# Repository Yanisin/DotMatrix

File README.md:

# DotMatrix

## What is this?

A STM32F070CB driving a LED DotMatrix.

## Prerequisities for building Firmware

  * You need an appropriate Cortex-M ARM toolchain. We suggest to use the
  ARM's [GNU Embedded Toolchain for Arm ](https://developer.arm.com/tools-and-software/open-source-software/developer-tools/gnu-toolchain/gnu-rm/downloads).
  Please note that the `gcc-arm-none-eabi` provided by Ubuntu 18.04 is currently broken and can't be used.

  * This project makes use of [libopencm3]()https://github.com/libopencm3/libopencm3) and [ChibiOS](http://www.chibios.org).
  In order to build `libopencm3` you need `Python 2`.

  * To download the firmware, you have two options:
     - Via USB: You need `dfu-util 0.9+` and a USB cable. Please not that `dfu-util 0.8` will not work.
     - Via SWD: You need `openocd` and a `ST-LINK v2 device`
  
  * Optional: `Docker`

You might be interested in some [libopencm3 examples here](https://github.com/libopencm3/libopencm3-examples).

The pull requests there might be an interesting source of information as well.

You will also want to have the manuals for your hardware at hand. These are the most important for software development:
 - Peripherals, memory layout, registers ... : [STM32F030x4/x6/x8/xC and STM32F070x6/xB MCUs](https://www.st.com/resource/en/reference_manual/dm00091010.pdf)
 - Pinouts, Electric Characteristcs, HW variants, clocks ...:
   [STM32F070CB Product Specification](https://www.st.com/resource/en/datasheet/stm32f070cb.pdf)
 - Exceptions (NVIC), instructions ... :
   [ARM® v7-M Architecture Reference Manual](https://static.docs.arm.com/ddi0403/eb/DDI0403E_B_armv7m_arm.pdf)

## Install & Build

Get the code:

    $ git clone https://github.com/libopencm3/libopencm3.git
    $ git clone https://github.com/ChibiOS/ChibiOS.git
    $ git clone https://github.com/Yanisin/DotMatrix.git

We provide a Dockerfile, containing the suggested toolchain, openocd, dfu-util and other tools as well.
You can build the container with:

    $ cd DotMatrix/
    DotMatrix$ docker build -t gcc-arm-none-eabi-8-2018-q4 .

Create a file named `settings.mk` in `DotMatrix/src` and provide an appropriate configuration.
You can use `DotMatrix/src/settings.mk.example` as input. This `settings.mk` works with the Docker container:

```
OPENCM3_DIR ?= /home/dev/app/src/libopencm3
CHIBIOS ?= /home/dev/app/src/ChibiOS
HW_VERSION = "HW_60x60_rev_0_5"
SUDO=
SIM=0
OOCD ?= openocd
OOCD_INTERFACE ?= stlink-v2-1
OOCD_TARGET ?= stm32f0x
```

You can start the container with:

    DotMatrix$ docker run -it --privileged --expose 4444 \
                  -v /dev/bus/usb:/dev/bus/usb \
                  -v `pwd`/../libopencm3:/home/dev/app/src/libopencm3 \
                  -v `pwd`/../ChibiOS:/home/dev/app/src/ChibiOS \
                  -v `pwd`:/home/dev/app \
                  gcc-arm-none-eabi-8-2018-q4:latest /bin/bash

You need to compile `libopencm3` before usage. This has to be done once.
With help of the toolchain container this is:

    dev@59e291eed30d:~/app$ cd src/libopencm3/
    dev@59e291eed30d:~/app/src/libopencm3$ make

ChibiOS is compiled on demand.

To compile the firmware / demo of your interest, just go to the directory and issue `$ make`. For instance:

    dev@59e291eed30d:~/app$ cd src/full/
    dev@59e291eed30d:~/app/src/full$ make

This should result in a binary `build/full.elf`.

### Content of the package

The software demos live in the src directory. There are are three main demos
avaiable:

- `src/stm32f070_miniblink` - a simple demo just blinking the LED
- `src/GameOfLife` - GameOfLife with all connected cells working together.
  Simple communication protocol over UART. The demo uses just libopencm3
  for HW interfacing.
- `src/full` - the 'catch all' demo. Includes GameOfLife and other applications
  that are selectable with an 'applet selector'. Provides a communication
  layer over I2C and UART. Automatically detects the topology of the boards
  at startup and chooses a 'master board'. Is based on an RTOS (ChibiOS).

There are also other small testing projects and a simulator that allows you to
run the 'full' demo on your host machine.

## Flashing

Flashing is done using the `make prg` and `make prg_usb` commands.
See `src/common.mk` for other makefile commands.

### SWD Interface

Attach the SWD interface of the MCU via stlink-v2 programmer and issue `$ make prg`

### USB DFU Bootloaders

There are two USB bootloaders.  One is burnt int the MCU from the manufacturer.
This one can be used in case of emergency to write "more specialized" bootloader stored 
in the FLASH, and that is used the flash the actual firmware.

The MCU itself has a bootloader burnt from the manufacture. This one requires
the Y1 oscillator popullated in order to work. It can be

#### Project Distributed Bootloader

There is a bootloader in `src/dfu`. Among other nice features this bootloader
allows to flash multiple interconnected boards at the same time.
Once compiled it can be flashed to ieach of the MCUs either using the stlink-v2
programer ( using `make prg` commad) or via the MCUs built in bootloader (using
the "make prg_bl" command).

If you want to use this bootloader (recommneded way), issue `$ make prg_usb` in
your project and connect the board over USB (or restart it, if it is already
connected. The flashing process will start as soon as the board reaches the
bootlader (you will see threee dots). If multiple boards are connected and
started at once, the firmware will be loaded to all of them.

The USB part of this bootloader seems to work even without Y1 resonator
populated, but the manufacturer does not say that it should be relyable.
If you have the the Y1 not populated keep this in mind.

#### MCU Manufacturers Bootloader

The MCU has a built in bootloader that is started if the BOOT0 pin is held hight
after reset is released. On the board there is reset circuitry with button.
If you hold this `reset` button for several seconds, you will get the board into
manufacturer provided bootloader. Among other ways (like USART, SPI, I2C) this
bootloader can program the flash via the USB DFU protocol. Use `make prg_bl` to
talk to this bootloader.  This can be used to flash the project bootloader or
have the wonderfull feeling of running bare-metal. If you want to run your
project without the project bootloader, You have to compile the demo with
`NO_BOOTLOADER=1`. 

Keep in mind that you can use this bootloader in USB DFU mode only if there is
the Y1 resonator present. If the Y1 is not present, you will need to use the
stlink-v2 or some other interface that this bootloader can handle even without
oscillator.  For details about this bootloader search for STs AN2606.

## Memory layout

Even though that you are programming C, it is important to know the memory
layout for debugging etc. The makefiles will take care of linking the code
at correct addreses.

ROM is mapped at 0x08000000 and the layout is as follows:

 Address | Size     | Usage
---------|----------|------------------------------------
0x0      | 0x4000   | Project Distributed Bootloader
0x4000   | 0x1C000  | Your application code (interrupt vectors, .text, .data)

RAM is mapped at 0x20000000 and the layout is as follows.

 Address | Size     | Usage
---------|----------|--------------------------------------------------------
0x0      | 0x100    | Interrupt vectors (loaded from ROM)
0x100    | 0x3F00   | Your application data (.data loaded from ROM, .bss)

For the location of IO registers for peripherals, consult the ST manual

# Hardware and mechanical parts
The currently used/latest HW is described in "pcb/60x60_dma". The board
is designed with KiCAD but there is the schematics exported in PDF 
and some assembly hints with list of needed parts are added as well.
The other folders in "src" are mostly unfinished various experiments/extension.

In the "mechanical" folder you can find the mechanical parts for 3D printing.
For each board PCB you will need one disp_support.stl.  The file is expected to
be printed with 0.4mm nozzle and 0.15mm layer height.  For connecting boards
you can use joint_cross_1_5m.stl for each corner (in older revision of the
board there is LED in the way so you need the use the one with the cuts for the
LED).

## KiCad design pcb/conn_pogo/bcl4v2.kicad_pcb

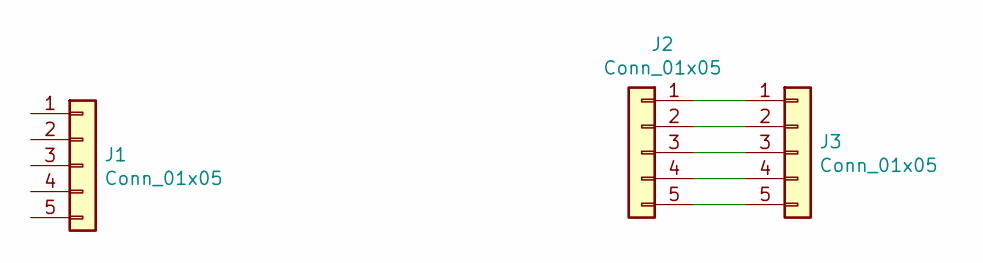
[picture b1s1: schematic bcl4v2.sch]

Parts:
J1: Conn_01x05; 5way_pogo_1.5mm_hole
J2, J3: Conn_01x05; 5way_pogo_pad

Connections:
unnamed: J2.1, J3.1
unnamed: J2.2, J3.2
unnamed: J2.3, J3.3
unnamed: J2.4, J3.4
unnamed: J2.5, J3.5

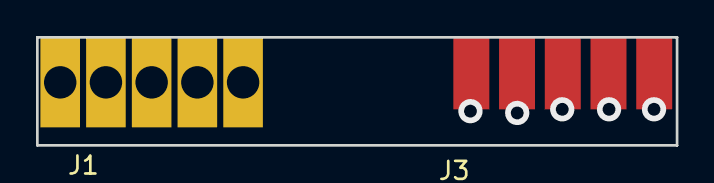
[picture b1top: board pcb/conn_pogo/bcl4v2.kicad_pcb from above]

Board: 2 copper layers, 35.5 x 6.0 mm, 3 parts (1 on the bottom side), 5 nets.

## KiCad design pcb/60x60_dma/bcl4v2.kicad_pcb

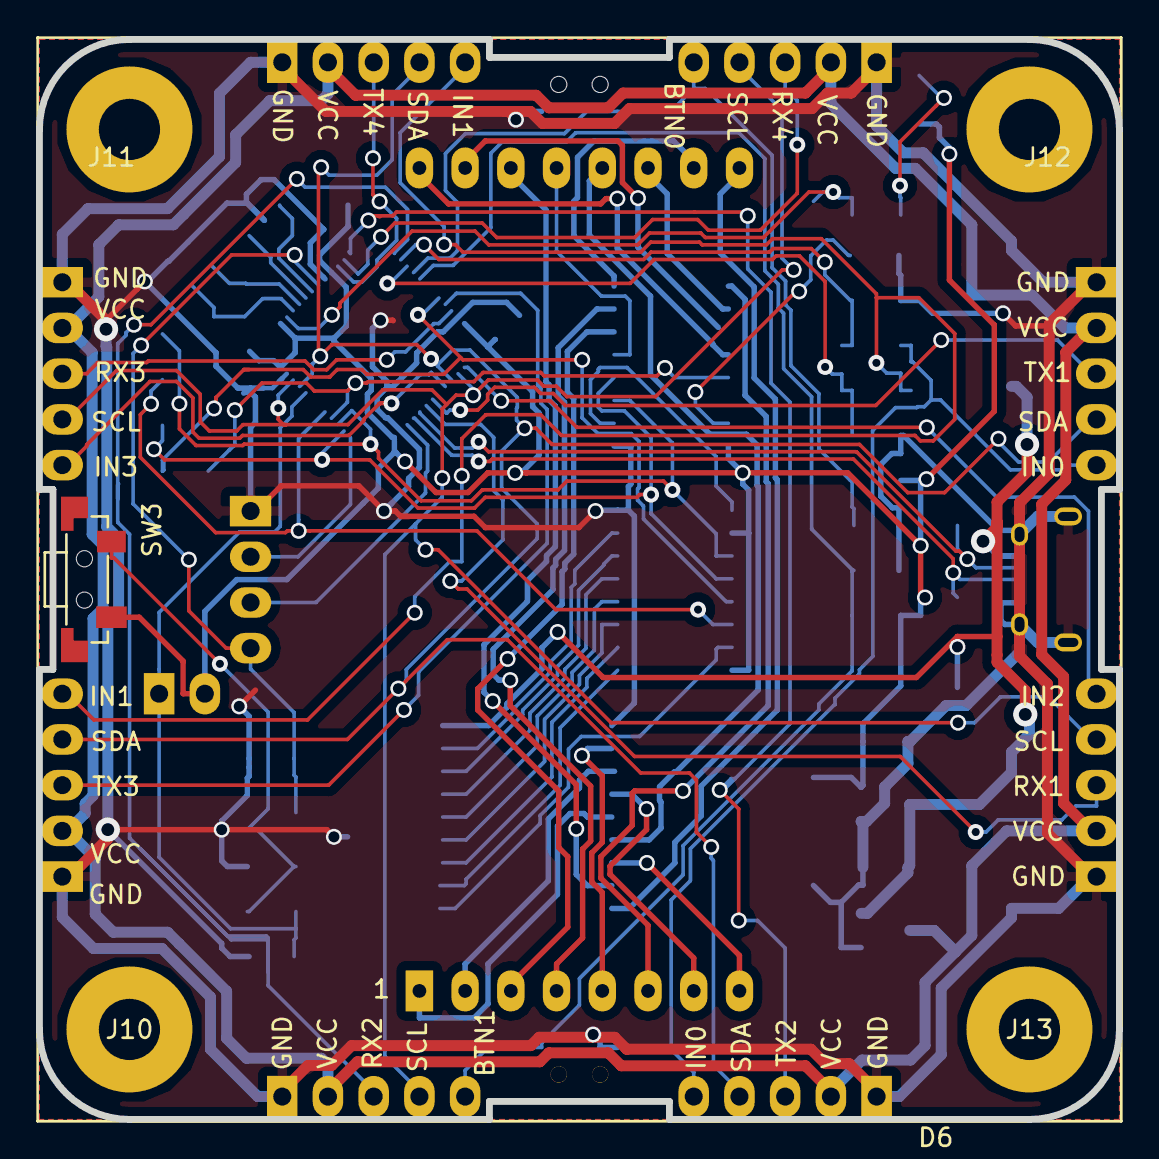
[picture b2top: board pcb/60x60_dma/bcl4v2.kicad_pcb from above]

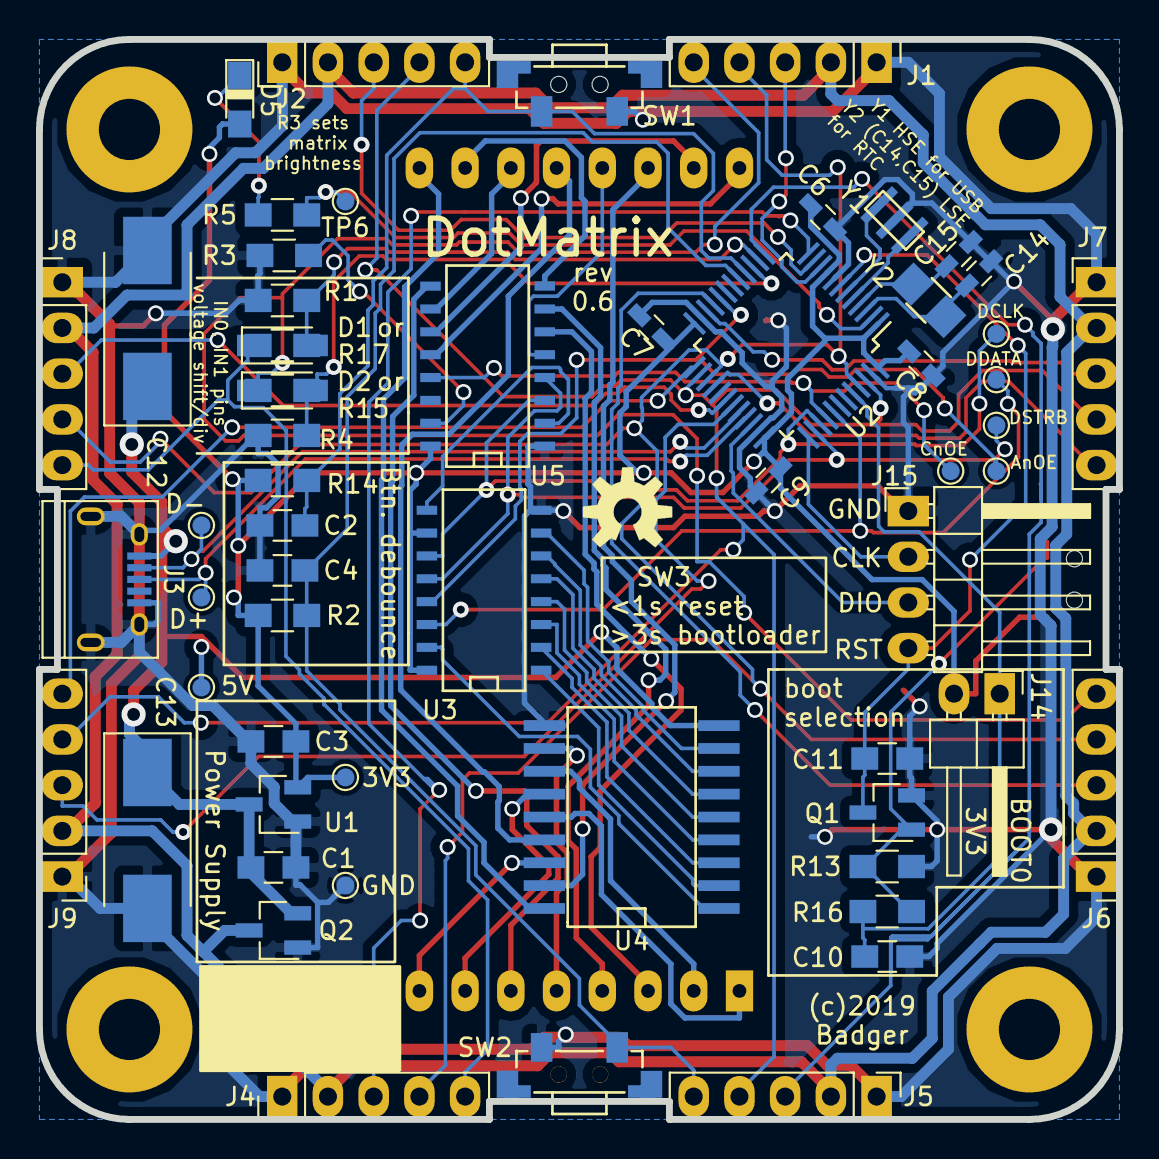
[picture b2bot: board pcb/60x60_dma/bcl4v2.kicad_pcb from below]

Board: 2 copper layers, 60.0 x 60.0 mm, 67 parts (61 on the bottom side), 66 nets.

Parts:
3V3, 5V: TestPoint; TestPoint_Pad_D1.0mm
AnOE: TestPoint; TestPoint_Pad_D1.0mm
C1, C3, C10: 4u7; C_0805_HandSoldering
C2, C4, C11: 100n; C_0805_HandSoldering
C6, C7, C8, C9: 100n; C_0603_HandSoldering
C12, C13: 220u; CP_Tantalum_Case-V_EIA-7343-20_Hand
C14, C15: 2pF; badger_C_0603_HandSoldering
CnOE: TestPoint; TestPoint_Pad_D1.0mm
D1, D2: Shottky; badger_D_SOD-123_hand
D5: LED; badger_LED_0805_HandSoldering
D6: LED_MATRIX_8x8; badger_LED_MATRIX_8x8_60.2mmx60.2mm
D+: TestPoint; TestPoint_Pad_D1.0mm
D-: TestPoint; TestPoint_Pad_D1.0mm
DCLK: TestPoint; TestPoint_Pad_D1.0mm
DDATA: TestPoint; TestPoint_Pad_D1.0mm
DSTRB: TestPoint; TestPoint_Pad_D1.0mm
GND: TestPoint; TestPoint_Pad_D1.0mm
J1, J2, J4, J5, J6, J7, J8, J9: Conn_01x05; badger_Pin_Hdr_1x05_2.54mm_handsolder
J3: USB_OTG; USB_Micro-B
J10, J11, J12, J13: Conn_01x01_Female; badger_mount_M3
J14: Conn_01x02; badger_Pin_Hdr_1x02_2.54mm_angled_handsolder
J15: Conn_01x04; badger_Pin_Hdr_1x04_2.54mm_angled_handsolder
LOGO1: OSHW-LOGOM; OSHW-LOGO-M
Q1: BSS138; badger_SOT-23_handsolder
Q2: IRLML6402; badger_SOT-23_handsolder
R1, R4, R13: 10k; R_0805_HandSoldering
R2, R14: 220k; R_0805_HandSoldering
R3: 470; R_0805_HandSoldering
R5: 1k; R_0805_HandSoldering
R15, R17: R; R_0805_HandSoldering
R16: 820k; R_0805_HandSoldering
SW1, SW2, SW3: SW_Push; badger_switch_K2-1112SA-A4SW-01
TP6: TestPoint; TestPoint_Pad_D1.0mm
U1: DS9166A-23; badger_SOT-23_handsolder
U2: STM32F070CBTx; badger_LQFP-48_7x7mm_Pitch0.5mm_handsolder
U3: 74HC595; SO-16-N
U4: TBD62783A; badger_SOIC-18W_7.5x11.6mm_Pitch1.27mm
U5: TLC5916; SO-16-N
Y1: Resonator; badger_CSTCE_G
Y2: ABS07-120-32.768kHz-T; badger_crystal_ABS07-120-xx_handsolder

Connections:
+3V3: 3V3.1, C3.1, C6.1, C7.1, C8.1, C9.1, D5.2, J14.2, R2.1, R14.1, SW3.1, U1.2, U2.1, U2.9, U2.24, U2.36, U2.48, U3.10, U3.16, U5.16
+5V: 5V.1, C1.1, C12.1, C13.1, J3.1, Q2.2, U1.3, U4.9
/AN_NOE: AnOE.1, U2.20, U3.13
/BOOT0: C10.1, J14.1, R16.1, U2.44
/BTN0: C2.2, J2.5, R14.2, SW1.1, U2.16
/BTN1: C4.2, J5.5, R2.2, SW2.1, U2.17
/CAT_NOE: CnOE.1, U2.40, U5.13
/DISP_CLK: DCLK.1, U2.39, U3.11, U5.3
/DISP_DATA: DDATA.1, U2.41, U3.14
/DISP_STROBE: DSTRB.1, U2.38, U3.12, U5.4
/I2C_SCL: J2.4, J5.4, J7.4, J9.4, U2.26, U2.46
/I2C_SDA: J1.4, J4.4, J6.4, J8.4, U2.27, U2.45
/IN0: D1.2, R1.2, R17.1, U2.14
/IN0P: D1.1, J4.5, J8.5, R17.2
/IN1: D2.2, R4.2, R15.1, U2.15
/IN1P: D2.1, J1.5, J6.5, R15.2
/IN2: J9.5, U2.25
/IN3: J7.5, U2.28
/LED: R5.2, TP6.1, U2.2
/LED_matrix/OUT_A0: D6.9, U4.18
/LED_matrix/OUT_A1: D6.14, U4.17
/LED_matrix/OUT_A2: D6.8, U4.16
/LED_matrix/OUT_A3: D6.12, U4.15
/LED_matrix/OUT_A4: D6.1, U4.14
/LED_matrix/OUT_A5: D6.7, U4.13
/LED_matrix/OUT_A6: D6.2, U4.12
/LED_matrix/OUT_A7: D6.5, U4.11
/LED_matrix/OUT_C0: D6.13, U5.5
/LED_matrix/OUT_C1: D6.3, U5.6
/LED_matrix/OUT_C2: D6.4, U5.7
/LED_matrix/OUT_C3: D6.10, U5.8
/LED_matrix/OUT_C4: D6.6, U5.9
/LED_matrix/OUT_C5: D6.11, U5.10
/LED_matrix/OUT_C6: D6.15, U5.11
/LED_matrix/OUT_C7: D6.16, U5.12
/LSE_IN: C14.1, U2.3, Y2.1
/LSE_OUT: C15.1, U2.4, Y2.2
/NRST: C11.1, J15.4, Q1.3, U2.7
/OSC_IN: U2.5, Y1.1
/OSC_OUT: U2.6, Y1.3
/SWCLK: J15.2, U2.37
/SWDIO: J15.3, U2.34
/UART_RX1: J9.3, U2.31
/UART_RX2: J5.3, U2.13
/UART_RX3: J7.3, U2.22
/UART_RX4: J2.3, U2.11
/UART_TX1: J8.3, U2.30
/UART_TX2: J4.3, U2.12
/UART_TX3: J6.3, U2.21
/UART_TX4: J1.3, U2.10
/USB_D+: D+.1, J3.3, U2.33
/USB_D-: D-.1, J3.2, U2.32
GND: C1.2, C2.1, C3.2, C4.1, C6.2, C7.2, C8.2, C9.2, C10.2, C11.2, C12.2, C13.2, C14.2, C15.2, GND.1, J1.1, J2.1, J3.5, J3.6, J4.1, J5.1, J6.1, J7.1, J8.1, J9.1, J15.1, Q1.2, Q2.1, R1.1, R3.2, R4.1, R13.2, SW1.2, SW2.2, U1.1, U2.8, U2.23, U2.35, U2.47, U3.8, U4.10, U5.1, Y1.2
unnamed: D5.1, R5.1
unnamed: Q1.1, R13.1, R16.2, SW3.2
unnamed: R3.1, U5.15
unnamed: U3.1, U4.2
unnamed: U3.2, U4.3
unnamed: U3.3, U4.4
unnamed: U3.4, U4.5
unnamed: U3.5, U4.6
unnamed: U3.6, U4.7
unnamed: U3.7, U4.8
unnamed: U3.9, U5.2
unnamed: U3.15, U4.1
VCC: J1.2, J2.2, J4.2, J5.2, J6.2, J7.2, J8.2, J9.2, Q2.3

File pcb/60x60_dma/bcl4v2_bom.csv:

"Reference"," Quantity"," Value","price [Kc]","price total","farnell","case"," Datasheet"
"C1 C10 C3 ",3,"4u7","2,6","7,8","https://cz.farnell.com/taiyo-yuden/emk212b7475kg-t/cap-4-7-f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","SMD 0805",
"C12 C13 ",2,"220u",16,32,"https://cz.farnell.com/avx/tajd107k010rnj/cap-100-f-10v-10-2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","EIA-7343-20",
"C14 C15 ",2,"2pF","0,67","1,34","https://cz.farnell.com/multicomp/mc0603n2r0c500ct/cap-2pf-50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","SMD 0805",
"C11 C2 C4 ",3,"100n","0,6","1,8","https://cz.farnell.com/multicomp/mcu0805r104kct/cap-0-1-f-50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","SMD 0805",
"C6 C7 C8 C9 ",4,"100n","0,6","2,4","https://cz.farnell.com/multicomp/mc0603b104m250ct/cap-0-1-f-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","SMD 0805",
"D1 D2 ",2,"Shottky","1,48","2,96","https://cz.farnell.com/taiwan-semiconductor/b0520lw-rhg/diod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","SOD-123",
"D5 ",1,"LED","0,3","0,3","ebay","SMD 0805",
"D6 ",1,"LED_MATRIX_8x8","70",70," https://www.ges.cz/cz/spl-32-GES06600358.html","LED_MATRIX_8x8_60.2mmx60.2mm",
"J1 J2 J4 J5 J6 J7 J8 J9 ",8,"Conn_01x05","0,7375","5,9","https://www.ges.cz/cz/pls-40s-GES06600276.html","Pin_Hdr_1x05_2.54mm",
,,,,0,,,
"J14 ",1,"Conn_01x02","0,3","0,3","https://www.ges.cz/cz/pls-40r1-GES06614710.html","Pin_Hdr_1x02_2.54mm_angled_handsolder",
"J15 ",1,"Conn_01x04","0,6","0,6","https://www.ges.cz/cz/pls-40r1-GES06614710.html","Pin_Hdr_1x04_2.54mm_angled_handsolder",
"J3 ",1,"USB_OTG",6,6,"https://cz.farnell.com/multicomp/mc001009/micro-usb-type-b-r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","USB_Micro-B",
"Q1 ",1,"BSS138","1,71","1,71","https://cz.farnell.com/nexperia/bss138p-215/mosfet-n-ch-60v-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","SOT-23",
"Q2 ",1,"IRLML6402","3,7","3,7","https://cz.farnell.com/infineon/irlml6402trpbf/mosfet-p-ch-2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","SOT-23",
"R14 R2 ",2,"220k",,0,,"SMD 0805",
"R15 R17 ",2,"R",,0,,"SMD 0805",
"R16 ",1,"820k",,0,,"SMD 0805",
"R3 ",1,"470",,0,,"SMD 0805",
"R1 R13 R4 ",3,"10k",,0,,"SMD 0805",
"R5 ",1,"1k",,0,,"SMD 0805",
"SW1 SW2 SW3 ",3,"SW_Push","1,6666666667","5,0000000001","lcsc","switch_K2-1112SA-A4SW-01",
,,,,0,,,
"U1 ",1,"	
MIC2091-1YM5-TR","3,4","3,4","https://cz.farnell.com/microchip/mic2091-1ym5-tr/power-switc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","SOT-23",
"U2 ",1,"STM32F070CBTx",40,40,"provided by badger","LQFP-48_7x7mm_Pitch0.5mm",
"U3 ",1,"74HC595","3,7","3,7","https://cz.farnell.com/on-semiconductor/mc74hc595adtr2g/ic-s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","SO-16-N","http://www.ti.com/lit/ds/symlink/sn74hc595.pdf"
"U4 ",1,"TBD62783A(replaced by TD62783AFG)",12,12,"https://www.ebay.com/itm/10pcs-NEW-TD62783AFG-SOP-18-TOSHIBA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","SOIC-18W_7.5x11.6mm_Pitch1.27mm","http://toshiba.semicon-storage.com/info/docget.jsp?did=30523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"
"U5 ",1,"TLC5916",24,24,"https://cz.farnell.com/texas-instruments/tlc5916id/ic-led-dr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","SO-16-N",
"Y1 ",1,"Resonator",10,10,,"CSTCE_G",
"Y2 ",1,"ABS07-120-32.768kHz-T",10,10,,"crystal_ABS07-120-xx","~"
,,,,,,,
"other:",,,,,,,
,4,"nylon spacers",,,,,
,4,"nylon nuts",,,,,
,4,"mini breadboard joints",,,,,

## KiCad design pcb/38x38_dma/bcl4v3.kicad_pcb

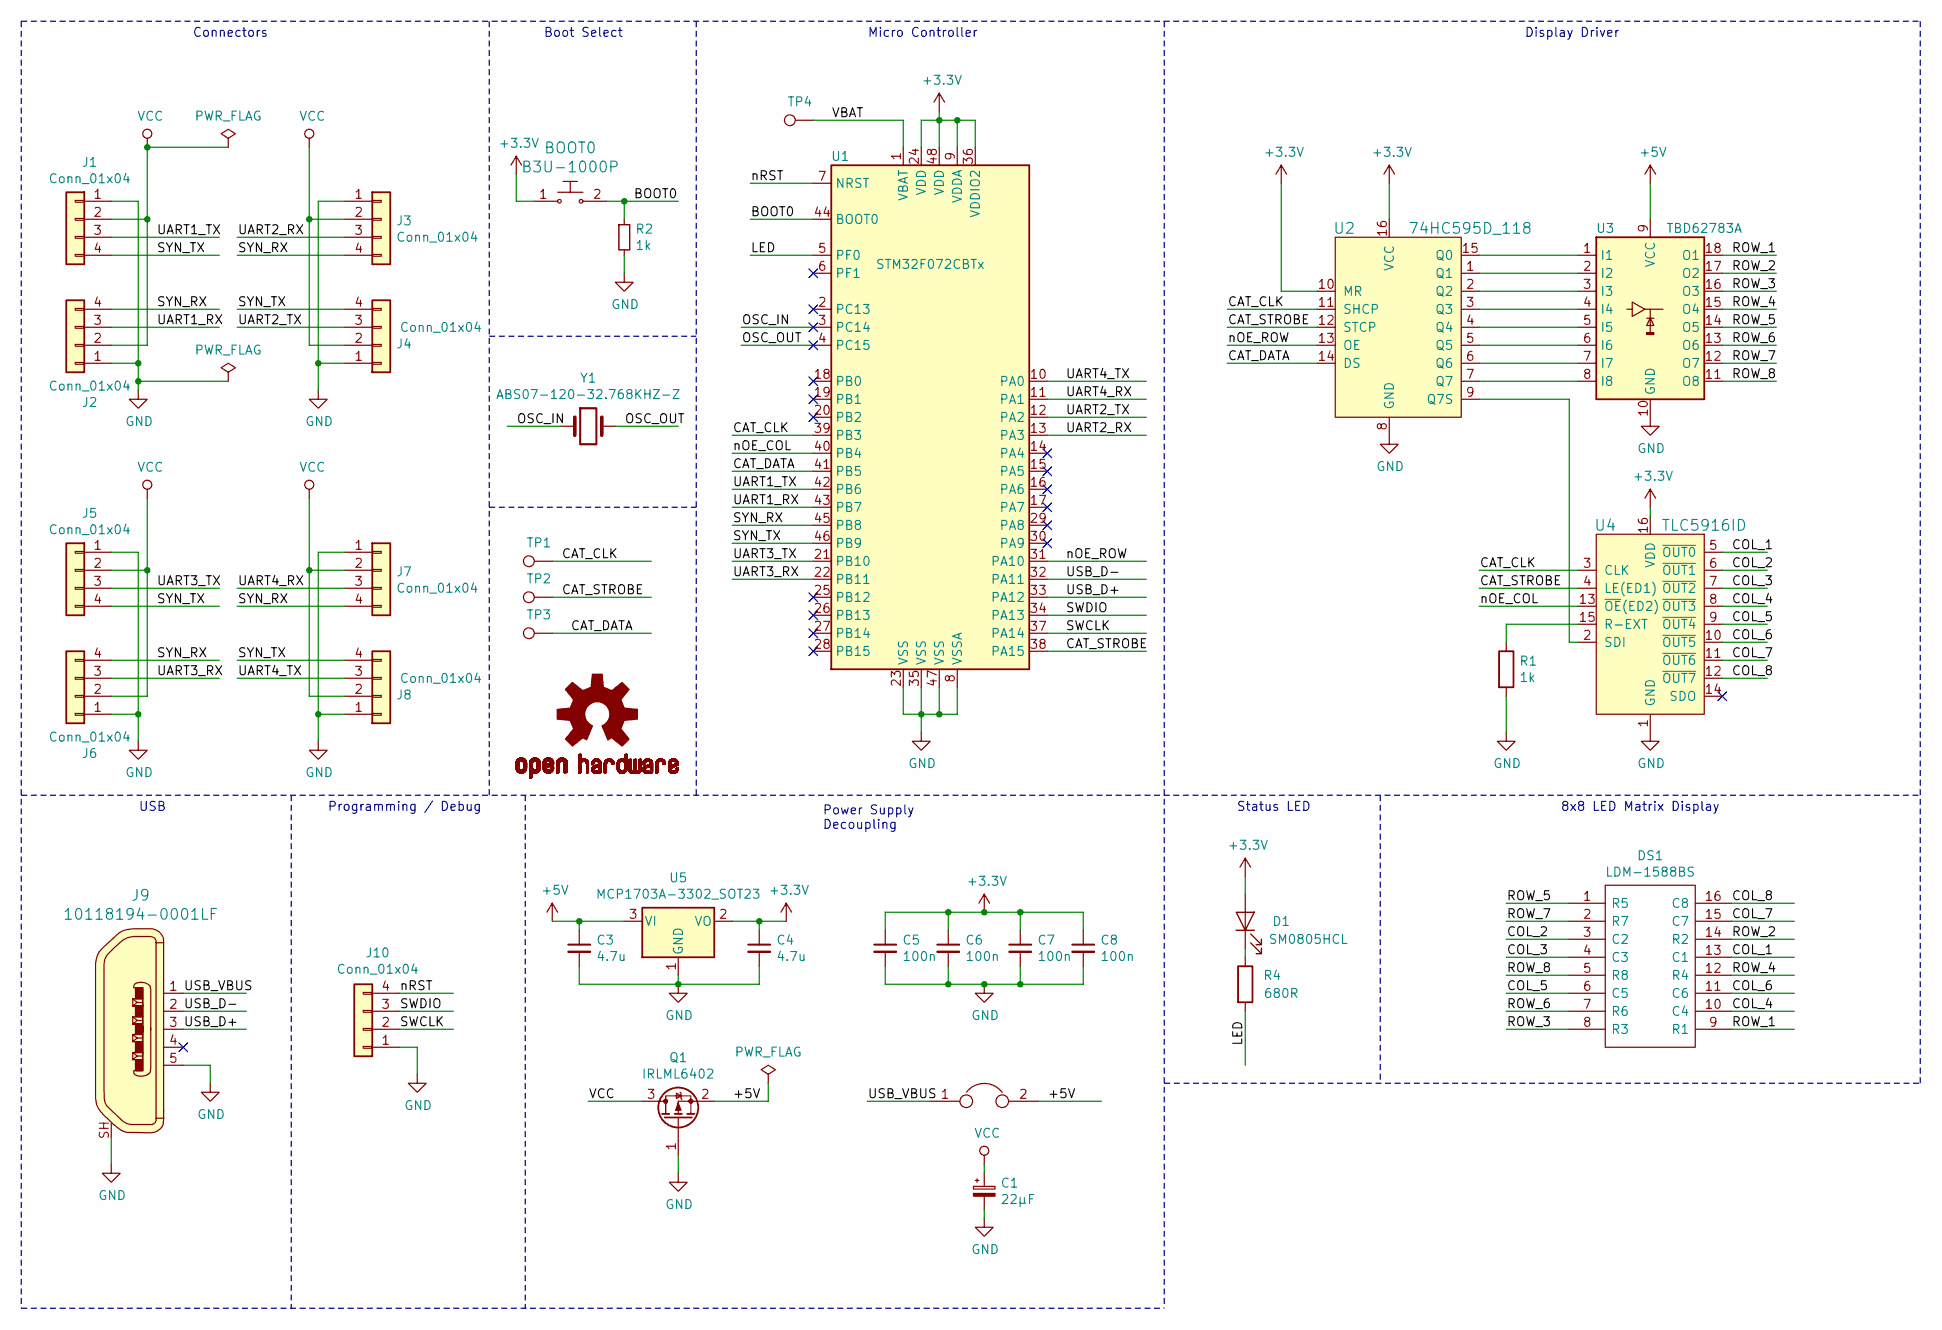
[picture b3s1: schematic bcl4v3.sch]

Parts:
BOOT0: B3U-1000P; Switch_Tactile_SMD_B3U-1000P; MPN B3U-1000P; Digi-Key_PN SW1020CT-ND
C1: 22µF; CP_EIA-3528-15_AVX-H_Pad1.50x2.35mm_HandSolder
C3, C4: 4.7u; C_0805_2012Metric_Pad1.15x1.40mm_HandSolder
C5, C6, C7, C8: 100n; C_0805_2012Metric_Pad1.15x1.40mm_HandSolder
D1: SM0805HCL; LED_0805_2012Metric_Castellated
DS1: LDM-1588BS; DIPS2794W50P254L3800H1065Q16N; Manufacturer_Part_Number TC15-11SRWA
J1, J2, J3, J4, J5, J6, J7, J8, J10: Conn_01x04; PinHeader_1x04_P2.54mm_Vertical
J9: 10118194-0001LF; USB_Micro_B_Female_10118194-0001LF; MPN 10118194-0001LF; Digi-Key_PN 609-4618-1-ND
JP1: Jumper; SMT-JUMPER_2_NC_TRACE_NO-SILK
LOGO1: OSHW-LOGOM; OSHW-LOGO-M
Q1: IRLML6402; SOT-23
R1, R2: 1k; R_0805_2012Metric_Pad1.15x1.40mm_HandSolder
R4: 680R; R_0805_2012Metric_Pad1.15x1.40mm_HandSolder
TP1, TP2, TP3, TP4: TestPoint; TestPoint_THTPad_1.0x1.0mm_Drill0.5mm
U1: STM32F072CBTx; LQFP-48_7x7mm_P0.5mm
U2: 74HC595D_118; TSSOP-16_4.4x5mm_P0.65mm; MPN 74HC595D,118; Digi-Key_PN 1727-2821-1-ND
U3: TBD62783A; SSOP-18_4.4x6.5mm_P0.65mm
U4: TLC5916ID; TSSOP-16_4.4x5mm_P0.65mm; MPN TLC5916ID; Digi-Key_PN 296-24383-5-ND
U5: MCP1703A-3302_SOT23; SOT-23
Y1: ABS07-120-32.768KHZ-Z; Crystal_SMD_MicroCrystal_CC7V-T1A-2Pin_3.2x1.5mm

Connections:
+3V3: BOOT0.1, C4.1, C5.1, C6.1, C7.1, C8.1, D1.2 (A), U1.9 (VDDA), U1.24 (VDD), U1.36 (VDDIO2), U1.48 (VDD), U2.10 (MR), U2.16 (VCC), U4.16 (VDD), U5.2 (VO)
+5V: C3.1, JP1.2, Q1.2 (S), U3.9 (VCC), U5.3 (VI)
/BOOT0: BOOT0.2, R2.1, U1.44 (BOOT0)
/CAT_CLK: TP1.1, U1.39 (PB3), U2.11 (SHCP), U4.3 (CLK)
/CAT_DATA: TP3.1, U1.41 (PB5), U2.14 (DS)
/CAT_STROBE: TP2.1, U1.38 (PA15), U2.12 (STCP), U4.4 (LE(ED1))
/COL_1: DS1.13 (C1), U4.5 (~OUT0)
/COL_2: DS1.3 (C2), U4.6 (~OUT1)
/COL_3: DS1.4 (C3), U4.7 (~OUT2)
/COL_4: DS1.10 (C4), U4.8 (~OUT3)
/COL_5: DS1.6 (C5), U4.9 (~OUT4)
/COL_6: DS1.11 (C6), U4.10 (~OUT5)
/COL_7: DS1.15 (C7), U4.11 (~OUT6)
/COL_8: DS1.16 (C8), U4.12 (~OUT7)
/LED: R4.2, U1.5 (PF0)
/OSC_IN: U1.3 (PC14), Y1.1
/OSC_OUT: U1.4 (PC15), Y1.2
/ROW_1: DS1.9 (R1), U3.18 (O1)
/ROW_2: DS1.14 (R2), U3.17 (O2)
/ROW_3: DS1.8 (R3), U3.16 (O3)
/ROW_4: DS1.12 (R4), U3.15 (O4)
/ROW_5: DS1.1 (R5), U3.14 (O5)
/ROW_6: DS1.7 (R6), U3.13 (O6)
/ROW_7: DS1.2 (R7), U3.12 (O7)
/ROW_8: DS1.5 (R8), U3.11 (O8)
/SWCLK: J10.2, U1.37 (PA14)
/SWDIO: J10.3, U1.34 (PA13)
/SYN_RX: J2.4, J3.4, J6.4, J7.4, U1.45 (PB8)
/SYN_TX: J1.4, J4.4, J5.4, J8.4, U1.46 (PB9)
/UART1_RX: J2.3, U1.43 (PB7)
/UART1_TX: J1.3, U1.42 (PB6)
/UART2_RX: J3.3, U1.13 (PA3)
/UART2_TX: J4.3, U1.12 (PA2)
/UART3_RX: J6.3, U1.22 (PB11)
/UART3_TX: J5.3, U1.21 (PB10)
/UART4_RX: J7.3, U1.11 (PA1)
/UART4_TX: J8.3, U1.10 (PA0)
/USB_D+: J9.3, U1.33 (PA12)
/USB_D-: J9.2, U1.32 (PA11)
/USB_VBUS: J9.1, JP1.1
/VBAT: TP4.1, U1.1 (VBAT)
/nOE_COL: U1.40 (PB4), U4.13 (~OE~(ED2))
/nOE_ROW: U1.31 (PA10), U2.13 (OE)
/nRST: J10.4, U1.7 (NRST)
GND: C1.2, C3.2, C4.2, C5.2, C6.2, C7.2, C8.2, J1.1, J2.1, J3.1, J4.1, J5.1, J6.1, J7.1, J8.1, J9.5, J9.SH, J10.1, Q1.1 (G), R1.2, R2.2, U1.8 (VSSA), U1.23 (VSS), U1.35 (VSS), U1.47 (VSS), U2.8 (GND), U3.10 (GND), U4.1 (GND), U5.1 (GND)
unnamed: D1.1 (K), R4.1
unnamed: R1.1, U4.15 (R-EXT)
unnamed: U2.1 (Q1), U3.2 (I2)
unnamed: U2.2 (Q2), U3.3 (I3)
unnamed: U2.3 (Q3), U3.4 (I4)
unnamed: U2.4 (Q4), U3.5 (I5)
unnamed: U2.5 (Q5), U3.6 (I6)
unnamed: U2.6 (Q6), U3.7 (I7)
unnamed: U2.7 (Q7), U3.8 (I8)
unnamed: U2.9 (Q7S), U4.2 (SDI)
unnamed: U2.15 (Q0), U3.1 (I1)
VCC: C1.1, J1.2, J2.2, J3.2, J4.2, J5.2, J6.2, J7.2, J8.2, Q1.3 (D)

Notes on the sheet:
8x8 LED Matrix Display
Status LED
Display Driver
Micro Controller
Power Supply Decoupling
Boot Select
Connectors
USB
Programming / Debug

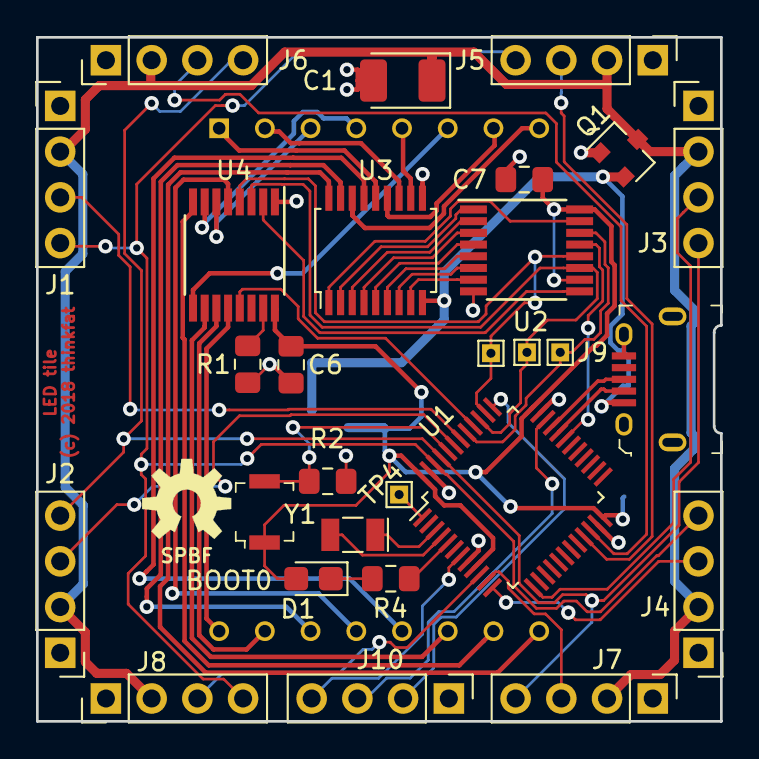
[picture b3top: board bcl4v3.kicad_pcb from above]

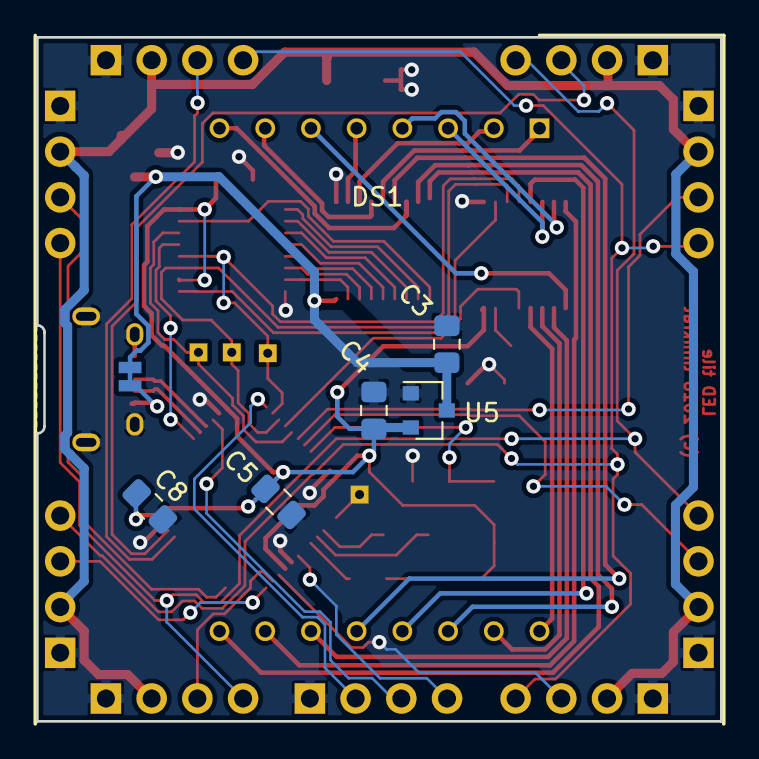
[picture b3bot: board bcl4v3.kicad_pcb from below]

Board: 2 copper layers, 38.0 x 38.0 mm, 36 parts (7 on the bottom side), 57 nets.

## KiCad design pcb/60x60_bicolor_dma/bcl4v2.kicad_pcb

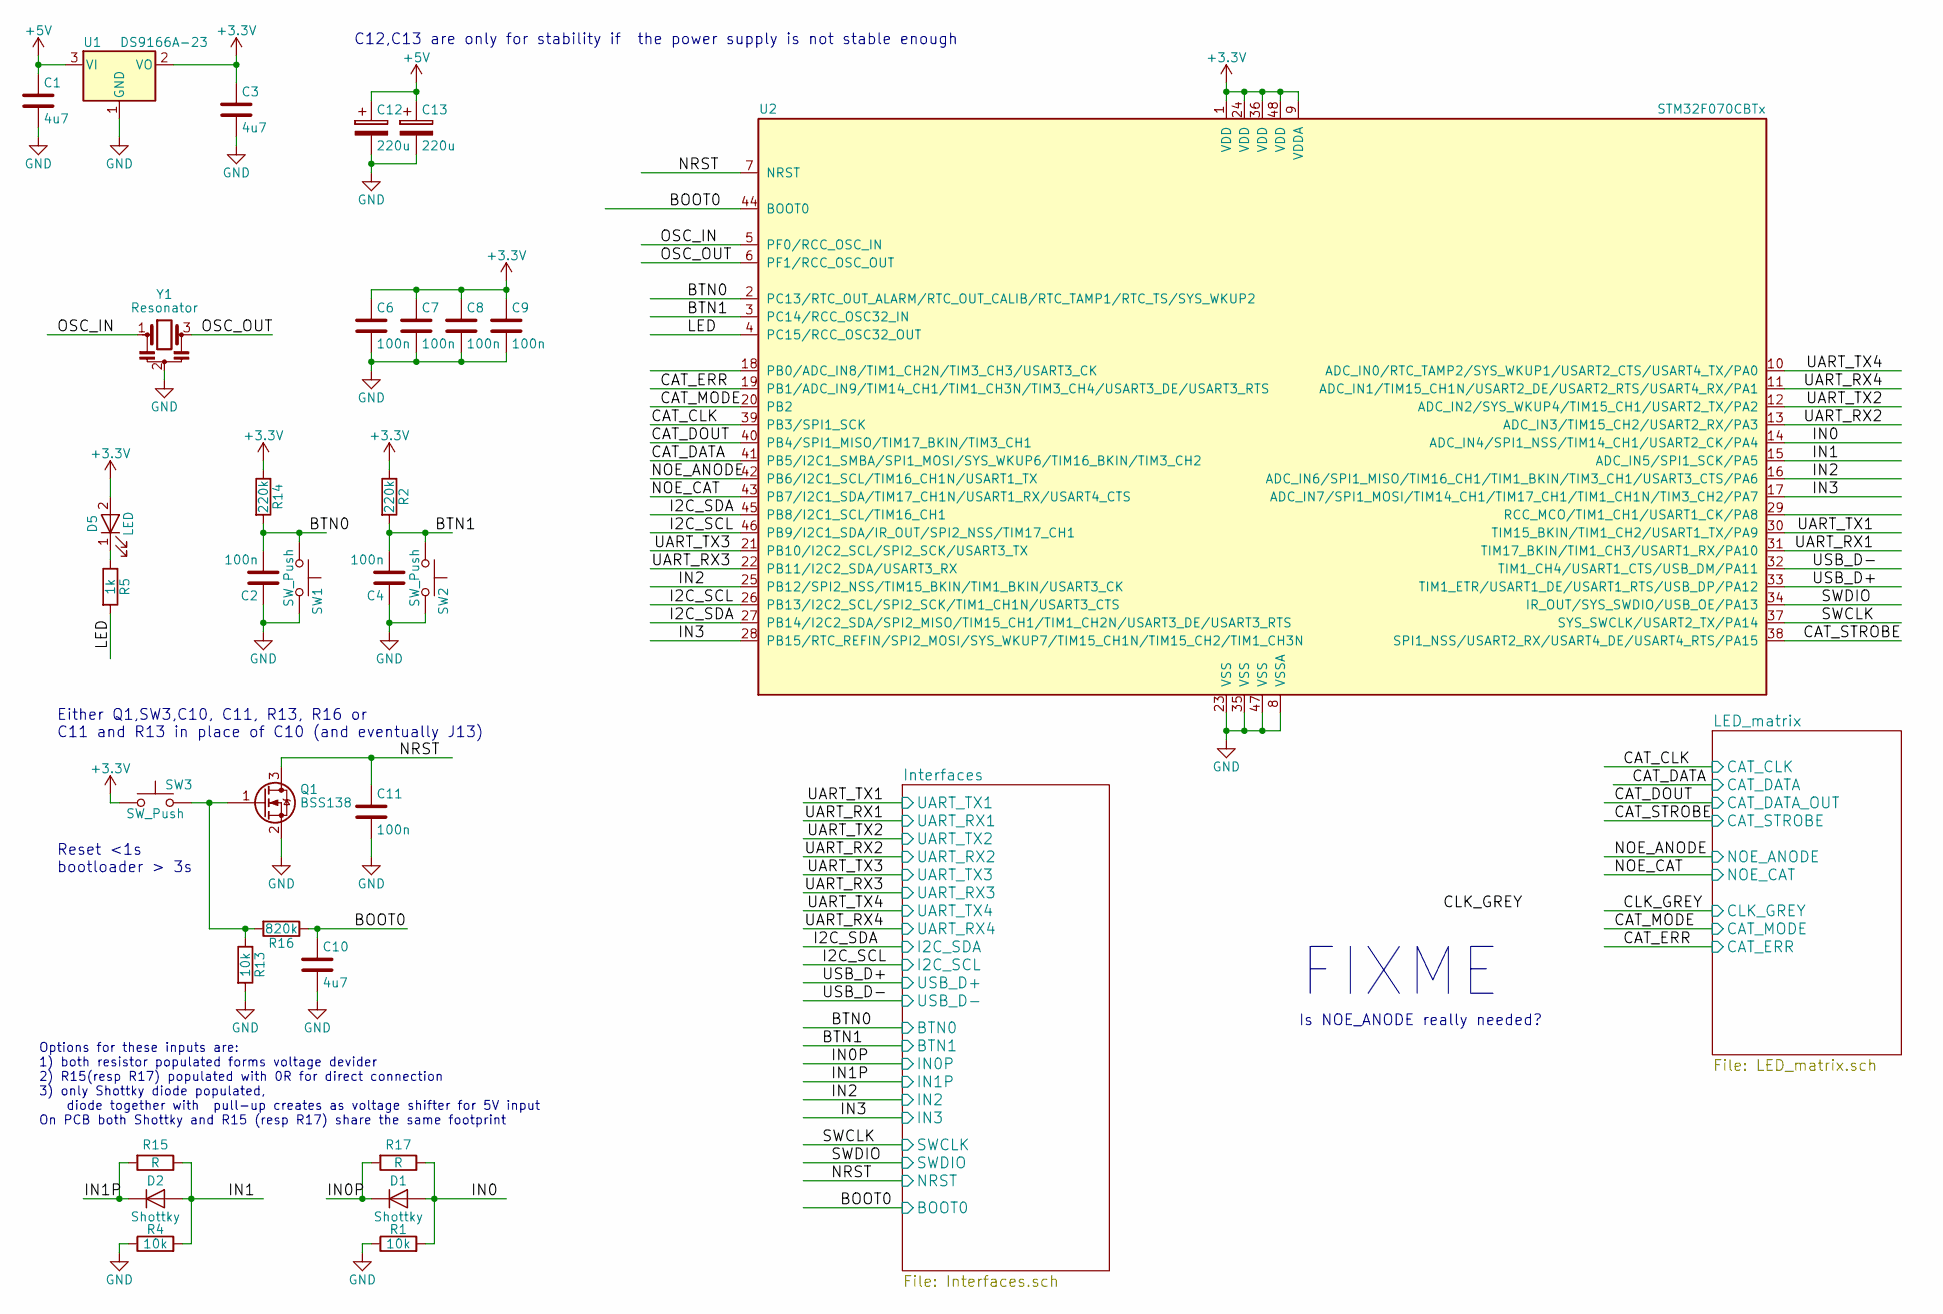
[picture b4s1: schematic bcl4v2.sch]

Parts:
C1, C3, C10: 4u7; C_0805_HandSoldering
C2, C4, C11: 100n; C_0805_HandSoldering
C6, C7, C8, C9: 100n; C_0603_HandSoldering
C12, C13: 220u; CP_Tantalum_Case-V_EIA-7343-20_Hand
D1, D2: Shottky; badger_D_SOD-123_hand
D5: LED; LED_0805_HandSoldering
Q1: BSS138; badger_SOT-23_handsolder
R1, R4, R13: 10k; R_0805_HandSoldering
R2, R14: 220k; R_0805_HandSoldering
R5: 1k; R_0805_HandSoldering
R15, R17: R; R_0805_HandSoldering
R16: 820k; R_0805_HandSoldering
SW1, SW2, SW3: SW_Push; badger_smd_button_KSS231G
U1: DS9166A-23; badger_SOT-23_handsolder
U2: STM32F070CBTx; badger_LQFP-48_7x7mm_Pitch0.5mm_handsolder
Y1: Resonator; badger_CSTCE_G

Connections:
+3V3: C3.1, C6.1, C7.1, C8.1, C9.1, D5.2 (A), R2.1, R14.1, SW3.1, U1.2 (VO), U2.1 (VDD), U2.9 (VDDA), U2.24 (VDD), U2.36 (VDD), U2.48 (VDD); also elsewhere on the board
+5V: C1.1, C12.1, C13.1, U1.3 (VI); also elsewhere on the board
/BOOT0: C10.1, R16.1, U2.44 (BOOT0); also elsewhere on the board
/BTN0: C2.2, R14.2, SW1.1, U2.2 (PC13/RTC_OUT_ALARM/RTC_OUT_CALIB/RTC_TA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); also elsewhere on the board
/BTN1: C4.2, R2.2, SW2.1, U2.3 (PC14/RCC_OSC32_IN); also elsewhere on the board
/CAT_CLK: U2.39 (PB3/SPI1_SCK); also elsewhere on the board
/CAT_DATA: U2.41 (PB5/I2C1_SMBA/SPI1_MOSI/SYS_WKUP6/TIM16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); also elsewhere on the board
/CAT_DOUT: U2.40 (PB4/SPI1_MISO/TIM17_BKIN/TIM3_CH1); also elsewhere on the board
/CAT_ERR: U2.19 (PB1/ADC_IN9/TIM14_CH1/TIM1_CH3N/TIM3_CH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); also elsewhere on the board
/CAT_MODE: U2.20 (PB2); also elsewhere on the board
/CAT_STROBE: U2.38 (SPI1_NSS/USART2_RX/USART4_DE/USART4_RTS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); also elsewhere on the board
/I2C_SCL: U2.26 (PB13/I2C2_SCL/SPI2_SCK/TIM1_CH1N/USART3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), U2.46 (PB9/I2C1_SDA/IR_OUT/SPI2_NSS/TIM17_CH1); also elsewhere on the board
/I2C_SDA: U2.27 (PB14/I2C2_SDA/SPI2_MISO/TIM15_CH1/TIM1_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), U2.45 (PB8/I2C1_SCL/TIM16_CH1); also elsewhere on the board
/IN0: D1.2 (A), R1.2, R17.1, U2.14 (ADC_IN4/SPI1_NSS/TIM14_CH1/USART2_CK/PA4)
/IN0P: D1.1 (K), R17.2; also elsewhere on the board
/IN1: D2.2 (A), R4.2, R15.1, U2.15 (ADC_IN5/SPI1_SCK/PA5)
/IN1P: D2.1 (K), R15.2; also elsewhere on the board
/IN2: U2.16 (ADC_IN6/SPI1_MISO/TIM16_CH1/TIM1_BKIN/T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), U2.25 (PB12/SPI2_NSS/TIM15_BKIN/TIM1_BKIN/USAR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); also elsewhere on the board
/IN3: U2.17 (ADC_IN7/SPI1_MOSI/TIM14_CH1/TIM17_CH1/T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), U2.28 (PB15/RTC_REFIN/SPI2_MOSI/SYS_WKUP7/TIM1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); also elsewhere on the board
/LED: R5.2, U2.4 (PC15/RCC_OSC32_OUT)
/NOE_ANODE: U2.42 (PB6/I2C1_SCL/TIM16_CH1N/USART1_TX); also elsewhere on the board
/NOE_CAT: U2.43 (PB7/I2C1_SDA/TIM17_CH1N/USART1_RX/USART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); also elsewhere on the board
/NRST: C11.1, Q1.3 (D), U2.7 (NRST); also elsewhere on the board
/OSC_IN: U2.5 (PF0/RCC_OSC_IN), Y1.1
/OSC_OUT: U2.6 (PF1/RCC_OSC_OUT), Y1.3
/SWCLK: U2.37 (SYS_SWCLK/USART2_TX/PA14); also elsewhere on the board
/SWDIO: U2.34 (IR_OUT/SYS_SWDIO/USB_OE/PA13); also elsewhere on the board
/UART_RX1: U2.31 (TIM17_BKIN/TIM1_CH3/USART1_RX/PA10); also elsewhere on the board
/UART_RX2: U2.13 (ADC_IN3/TIM15_CH2/USART2_RX/PA3); also elsewhere on the board
/UART_RX3: U2.22 (PB11/I2C2_SDA/USART3_RX); also elsewhere on the board
/UART_RX4: U2.11 (ADC_IN1/TIM15_CH1N/USART2_DE/USART2_RTS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); also elsewhere on the board
/UART_TX1: U2.30 (TIM15_BKIN/TIM1_CH2/USART1_TX/PA9); also elsewhere on the board
/UART_TX2: U2.12 (ADC_IN2/SYS_WKUP4/TIM15_CH1/USART2_TX/P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); also elsewhere on the board
/UART_TX3: U2.21 (PB10/I2C2_SCL/SPI2_SCK/USART3_TX); also elsewhere on the board
/UART_TX4: U2.10 (ADC_IN0/RTC_TAMP2/SYS_WKUP1/USART2_CTS/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); also elsewhere on the board
/USB_D+: U2.33 (TIM1_ETR/USART1_DE/USART1_RTS/USB_DP/PA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); also elsewhere on the board
/USB_D-: U2.32 (TIM1_CH4/USART1_CTS/USB_DM/PA11); also elsewhere on the board
GND: C1.2, C2.1, C3.2, C4.1, C6.2, C7.2, C8.2, C9.2, C10.2, C11.2, C12.2, C13.2, Q1.2 (S), R1.1, R4.1, R13.2, SW1.2, SW2.2, U1.1 (GND), U2.8 (VSSA), U2.23 (VSS), U2.35 (VSS), U2.47 (VSS), Y1.2; also elsewhere on the board
unnamed: D5.1 (K), R5.1
unnamed: Q1.1 (G), R13.1, R16.2, SW3.2

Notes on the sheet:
Options for these inputs are: 1) both resistor populated forms voltage devider 2) R15(resp R17) populated with 0R for direct connection 3) only Shottky diode populated, diode together with pull-up creates as voltage shifter for 5V input On PCB both Shottky and R15 (resp R17) share the same footprint
Reset <1s bootloader > 3s
Either Q1,SW3,C10, C11, R13, R16 or C11 and R13 in place of C10 (and eventually J13)
C12,C13 are only for stability if the power supply is not stable enough
FIXME
Is NOE_ANODE really needed?

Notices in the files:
pcb/38x38_dma/bcl4v3.kicad_pcb:
(c) 2018 thinkfat
pcb/60x60_bicolor_dma/bcl4v2.kicad_pcb:
(c)2018
